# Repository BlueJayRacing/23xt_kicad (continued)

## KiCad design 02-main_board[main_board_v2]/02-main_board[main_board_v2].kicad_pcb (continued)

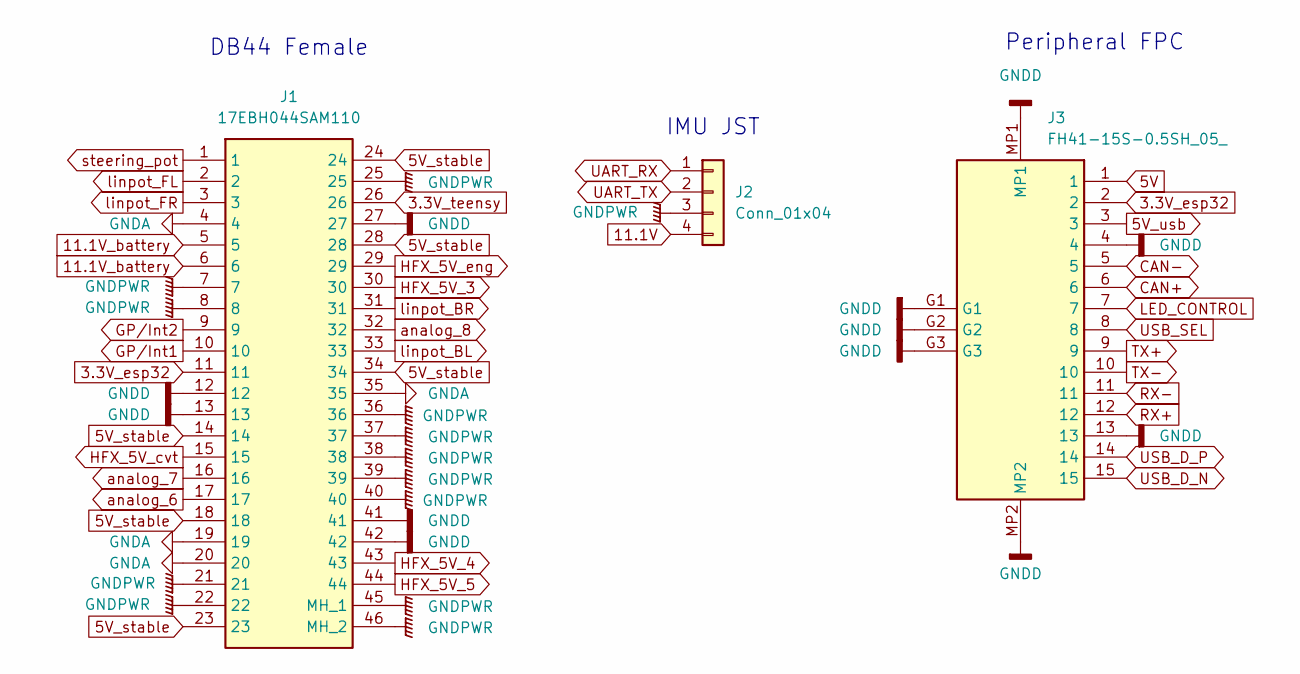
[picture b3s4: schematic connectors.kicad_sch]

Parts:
J1: 17EBH044SAM110; Manufacturer_Part_Number 17EBH044SAM110
J2: Conn_01x04; JST_EH_B4B-EH-A_1x04_P2.50mm_Vertical
J3: FH41-15S-0.5SH_05_; FH4115S05SH05; Mouser Part Number 798-FH4115S05SH05

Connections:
3.3V_esp32: J1.11, J3.2; also elsewhere on the board
3.3V_teensy: J1.26; also elsewhere on the board
5V: J3.1; also elsewhere on the board
5V_stable: J1.14, J1.18, J1.23, J1.24, J1.28, J1.34; also elsewhere on the board
5V_usb: J3.3; also elsewhere on the board
11.1V: J2.4; also elsewhere on the board
11.1V_battery: J1.5, J1.6; also elsewhere on the board
CAN+: J3.6; also elsewhere on the board
CAN-: J3.5; also elsewhere on the board
GNDA: J1.4, J1.7, J1.8, J1.12, J1.13, J1.19, J1.20, J1.21, J1.22, J1.25, J1.27, J1.35, J1.36, J1.37, J1.38, J1.39, J1.40, J1.41, J1.42, J1.45 (MH_1), J1.46 (MH_2), J2.3, J3.4, J3.13, J3.G1, J3.G2, J3.G3, J3.MP1, J3.MP2; also elsewhere on the board
GP/Int1: J1.10; also elsewhere on the board
GP/Int2: J1.9; also elsewhere on the board
HFX_5V_3: J1.30; also elsewhere on the board
HFX_5V_4: J1.43; also elsewhere on the board
HFX_5V_5: J1.44; also elsewhere on the board
HFX_5V_cvt: J1.15; also elsewhere on the board
HFX_5V_eng: J1.29; also elsewhere on the board
LED_CONTROL: J3.7; also elsewhere on the board
RX+: J3.12; also elsewhere on the board
RX-: J3.11; also elsewhere on the board
TX+: J3.9; also elsewhere on the board
TX-: J3.10; also elsewhere on the board
UART_RX: J2.1; also elsewhere on the board
UART_TX: J2.2; also elsewhere on the board
USB_D_N: J3.15; also elsewhere on the board
USB_D_P: J3.14; also elsewhere on the board
USB_SEL: J3.8; also elsewhere on the board
analog_6: J1.17; also elsewhere on the board
analog_7: J1.16; also elsewhere on the board
analog_8: J1.32; also elsewhere on the board
linpot_BL: J1.33; also elsewhere on the board
linpot_BR: J1.31; also elsewhere on the board
linpot_FL: J1.2; also elsewhere on the board
linpot_FR: J1.3; also elsewhere on the board
steering_pot: J1.1; also elsewhere on the board

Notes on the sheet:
DB44 Female
Peripheral FPC
IMU JST

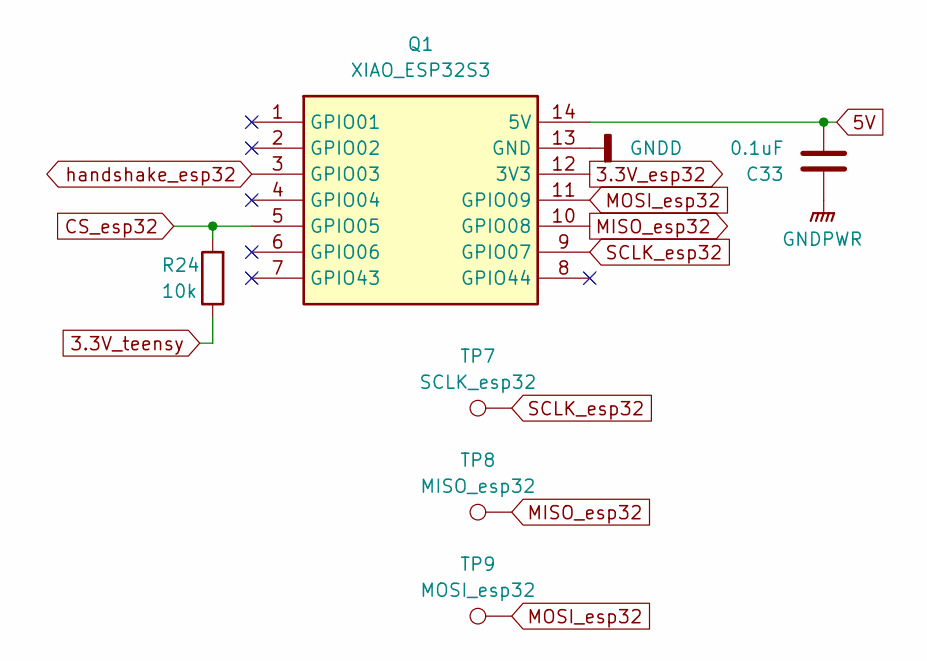
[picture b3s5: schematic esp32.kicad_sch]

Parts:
C33: 0.1uF; C_0603_1608Metric; MPN CC0603KRX7R9BB104; LCSC C14663
Q1: XIAO_ESP32S3; Manufacturer_Part_Number XIAO ESP32S3
R24: 10k; R_0603_1608Metric; MPN CRCW060310K0FKEA; LCSC C25804
TP7: SCLK_esp32; TestPoint_Pad_1.0x1.0mm
TP8: MISO_esp32; TestPoint_Pad_1.0x1.0mm
TP9: MOSI_esp32; TestPoint_Pad_1.0x1.0mm

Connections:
3.3V_esp32: Q1.12 (3V3); also elsewhere on the board
3.3V_teensy: R24.1; also elsewhere on the board
5V: C33.2, Q1.14 (5V); also elsewhere on the board
CS_esp32: Q1.5 (GPIO05), R24.2; also elsewhere on the board
GNDA: C33.1, Q1.13 (GND); also elsewhere on the board
MISO_esp32: Q1.10 (GPIO08), TP8.1 (1_1); also elsewhere on the board
MOSI_esp32: Q1.11 (GPIO09), TP9.1 (1_1); also elsewhere on the board
SCLK_esp32: Q1.9 (GPIO07), TP7.1 (1_1); also elsewhere on the board
handshake_esp32: Q1.3 (GPIO03); also elsewhere on the board

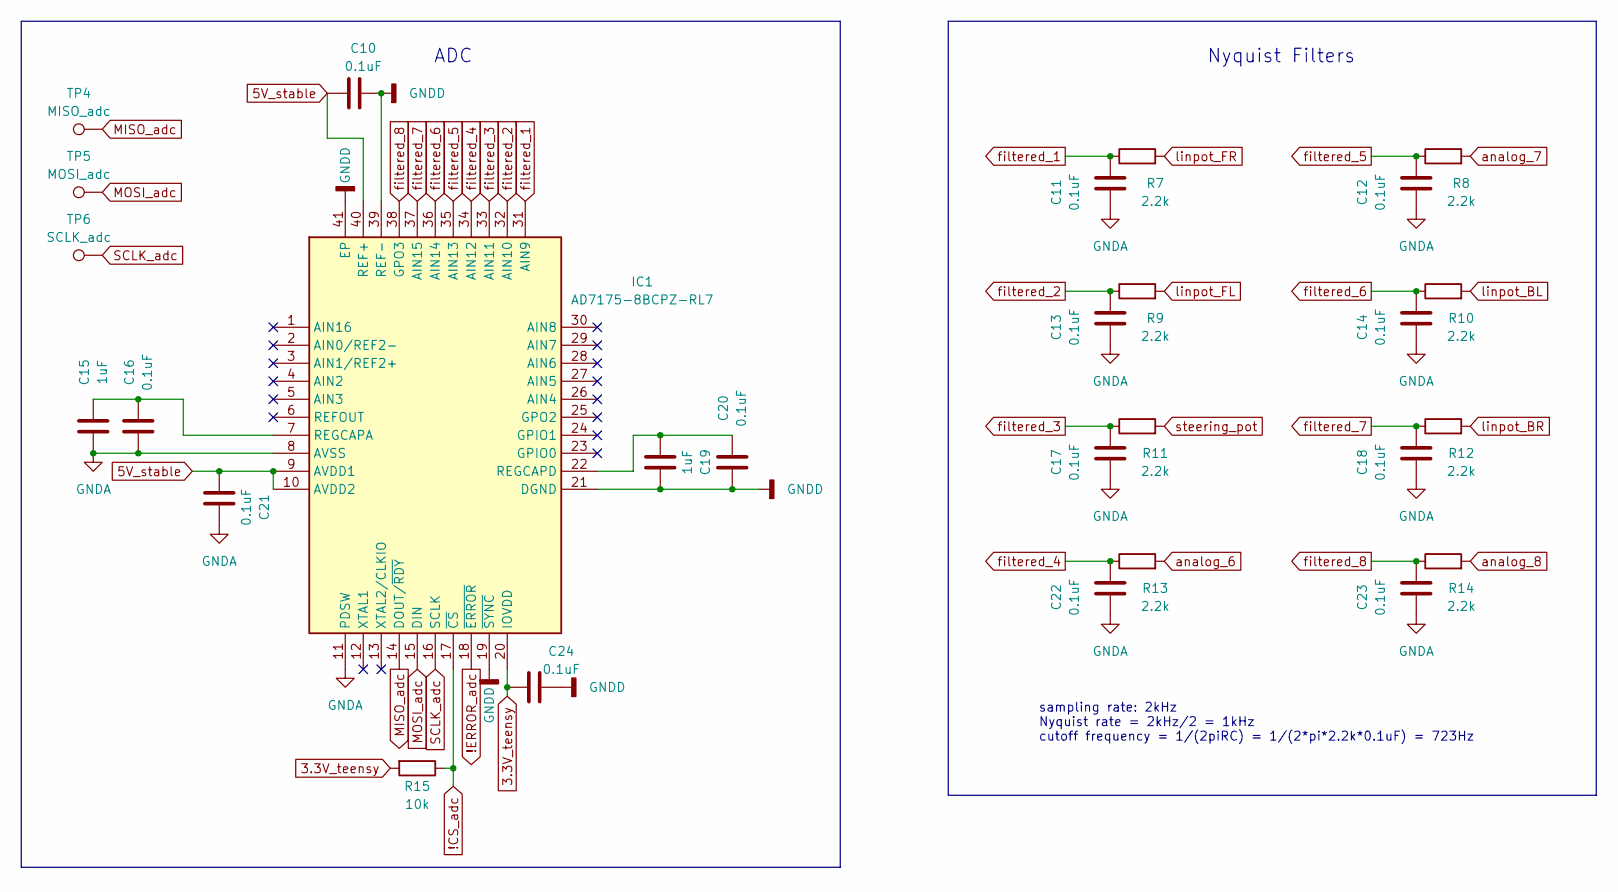
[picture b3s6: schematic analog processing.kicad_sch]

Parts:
C10, C11, C12, C13, C14, C16, C17, C18, C20, C21, C22, C23, C24: 0.1uF; C_0603_1608Metric; MPN CC0603KRX7R9BB104; LCSC C14663
C15, C19: 1uF; C_0603_1608Metric; MPN CL10A105KA8NFNC; LCSC C15849
IC1: AD7175-8BCPZ-RL7; Manufacturer_Part_Number AD7175-8BCPZ-RL7; Mouser Part Number 584-AD7175-8BCPZ-RL7
R7, R8, R9, R10, R11, R12, R13, R14: 2.2k; R_0603_1608Metric; MPN RC0603FR-072K2L; LCSC C4190
R15: 10k; R_0603_1608Metric; MPN CRCW060310K0FKEA; LCSC C25804
TP4: MISO_adc; TestPoint_Pad_1.0x1.0mm
TP5: MOSI_adc; TestPoint_Pad_1.0x1.0mm
TP6: SCLK_adc; TestPoint_Pad_1.0x1.0mm

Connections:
3.3V_teensy: C24.1, IC1.20 (IOVDD), R15.2; also elsewhere on the board
5V_stable: C10.1, C21.1, IC1.9 (AVDD1), IC1.10 (AVDD2), IC1.40 (REF+); also elsewhere on the board
!CS_adc: IC1.17 (~CS), R15.1; also elsewhere on the board
!ERROR_adc: IC1.18 (~ERROR); also elsewhere on the board
GNDA: C10.2, C11.1, C12.1, C13.1, C14.1, C15.1, C16.1, C17.1, C18.1, C19.2, C20.1, C21.2, C22.1, C23.1, C24.2, IC1.8 (AVSS), IC1.11 (PDSW), IC1.19 (~SYNC), IC1.21 (DGND), IC1.39 (REF-), IC1.41 (EP); also elsewhere on the board
MISO_adc: IC1.14 (DOUT/~RDY), TP4.1 (1_1); also elsewhere on the board
MOSI_adc: IC1.15 (DIN), TP5.1 (1_1); also elsewhere on the board
unnamed: C15.2, C16.2, IC1.7 (REGCAPA)
unnamed: C19.1, C20.2, IC1.22 (REGCAPD)
SCLK_adc: IC1.16 (SCLK), TP6.1 (1_1); also elsewhere on the board
analog_6: R13.2; also elsewhere on the board
analog_7: R8.2; also elsewhere on the board
analog_8: R14.2; also elsewhere on the board
filtered_1: C11.2, IC1.31 (AIN9), R7.1
filtered_2: C13.2, IC1.32 (AIN10), R9.1
filtered_3: C17.2, IC1.33 (AIN11), R11.1
filtered_4: C22.2, IC1.34 (AIN12), R13.1
filtered_5: C12.2, IC1.35 (AIN13), R8.1
filtered_6: C14.2, IC1.36 (AIN14), R10.1
filtered_7: C18.2, IC1.37 (AIN15), R12.1
filtered_8: C23.2, IC1.38 (GPO3), R14.1
linpot_BL: R10.2; also elsewhere on the board
linpot_BR: R12.2; also elsewhere on the board
linpot_FL: R9.2; also elsewhere on the board
linpot_FR: R7.2; also elsewhere on the board
steering_pot: R11.2; also elsewhere on the board

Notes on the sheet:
Nyquist Filters
sampling rate: 2kHz Nyquist rate = 2kHz/2 = 1kHz cutoff frequency = 1/(2piRC) = 1/(2*pi*2.2k*0.1uF) = 723Hz
ADC

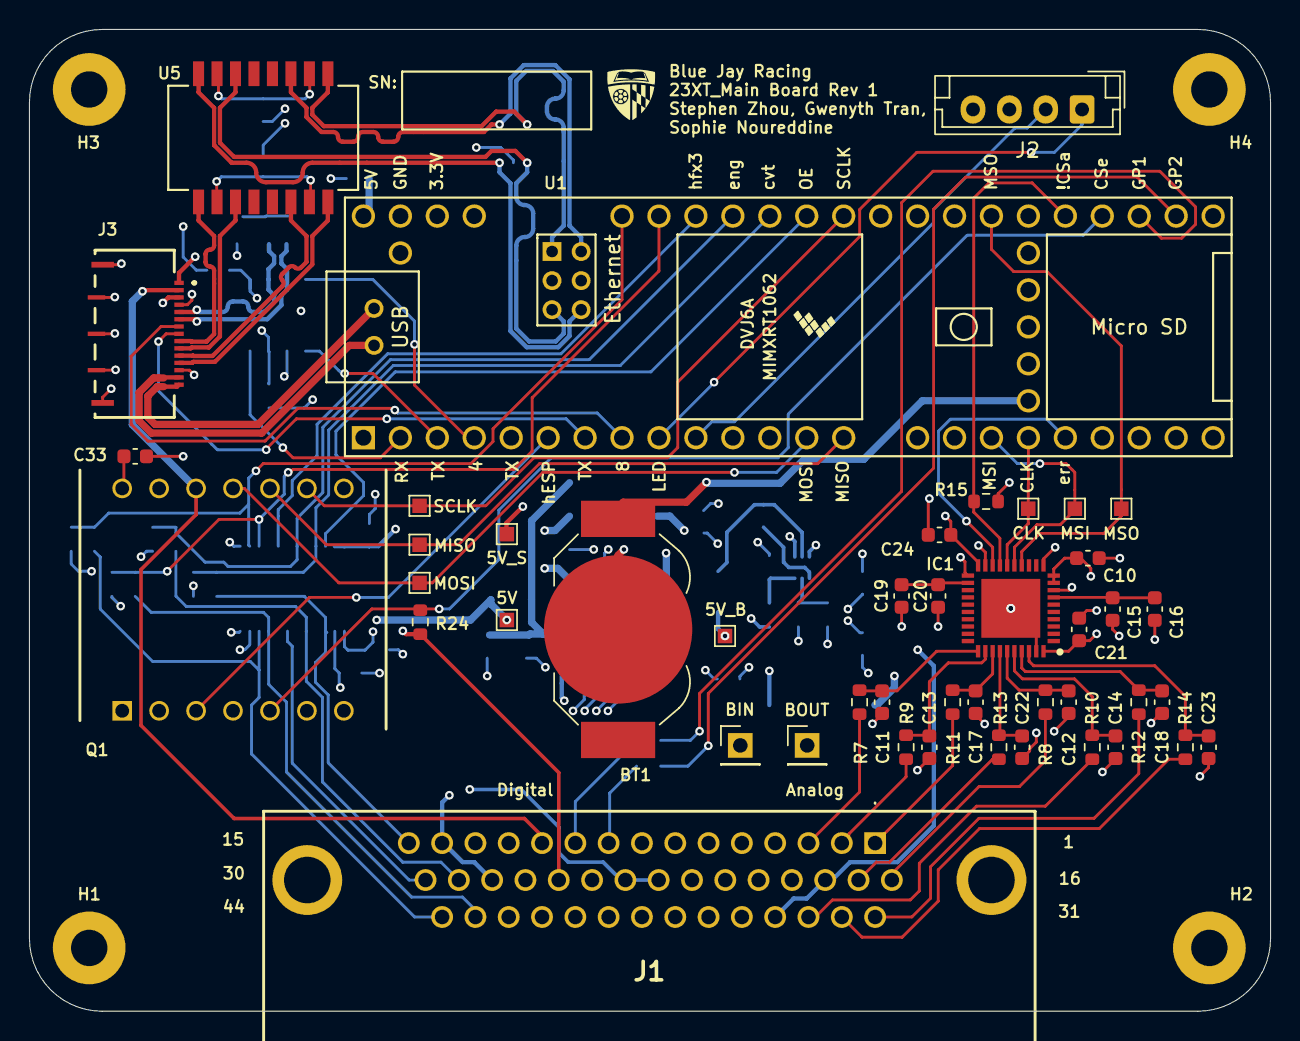
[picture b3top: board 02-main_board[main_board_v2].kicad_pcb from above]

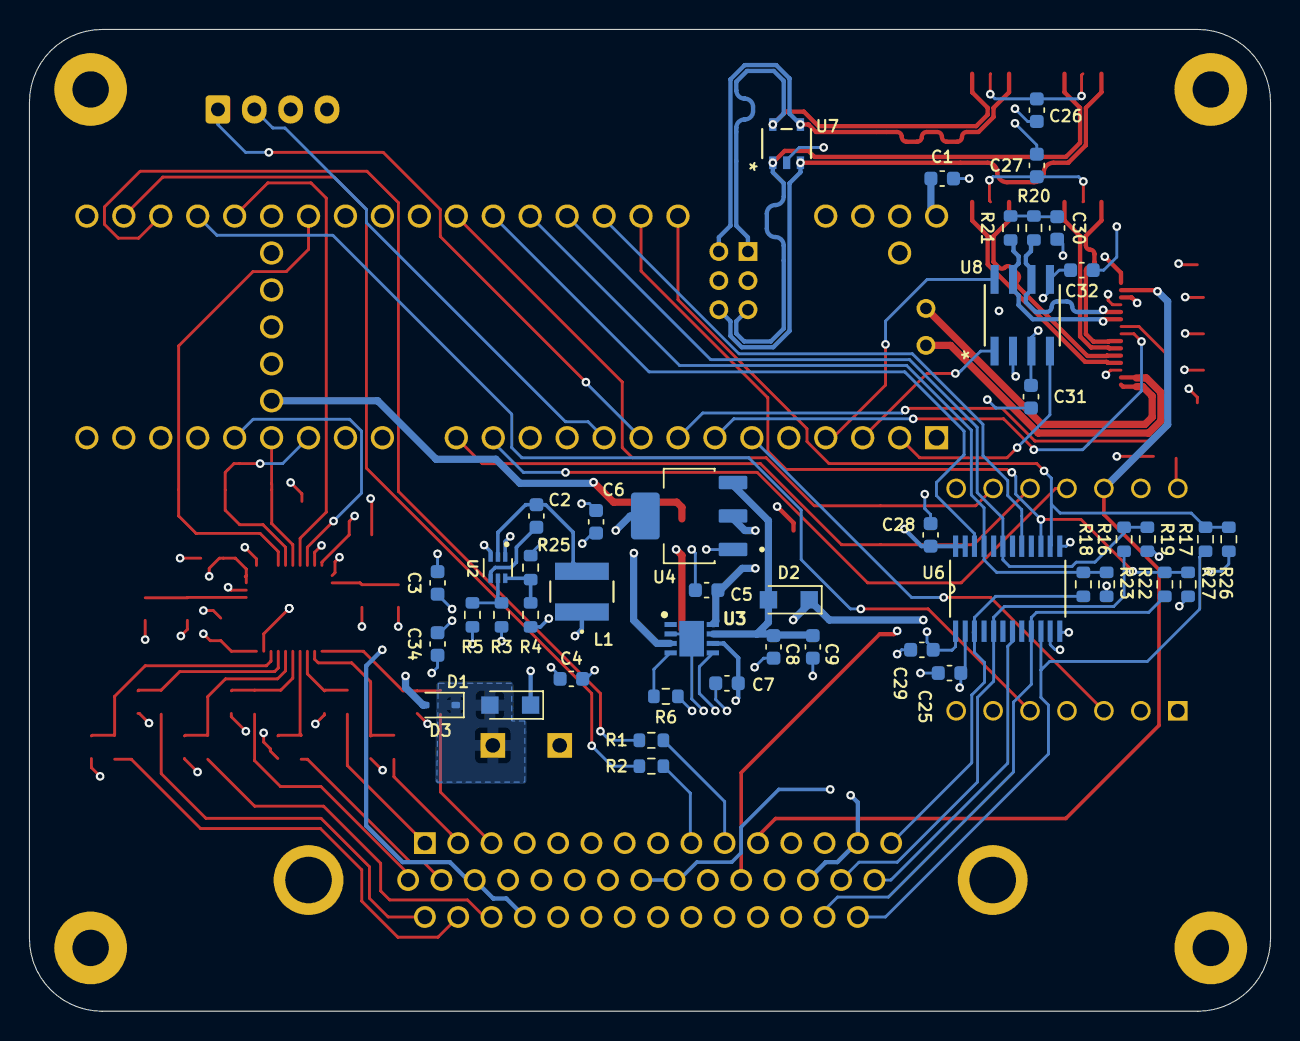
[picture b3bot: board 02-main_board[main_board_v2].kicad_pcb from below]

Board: 4 copper layers, 85.3 x 67.5 mm, 94 parts (45 on the bottom side), 82 nets.

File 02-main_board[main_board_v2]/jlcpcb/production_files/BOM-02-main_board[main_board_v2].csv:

Comment,Designator,Footprint,LCSC,Quantity
0.1uF,"C1,C10,C11,C12,C13,C14,C16,C17,C18,C2,C20,C21,C22,C23,C24,C25,C26,C27,C28,C29,C30,C31,C32,C33,C34,C5,C7,C8",C_0603_1608Metric,C14663,28
10k,"R15,R24,R3",R_0603_1608Metric,C25804,3
10uF,C3,C_0603_1608Metric,C96446,1
12k,R5,R_0603_1608Metric,C22790,1
1uF,"C15,C19,C6,C9",C_0603_1608Metric,C15849,4
2.2k,"R10,R11,R12,R13,R14,R7,R8,R9",R_0603_1608Metric,C4190,8
22uF,C4,C_0603_1608Metric,C59461,1
3.3uH,L1,IND_TAIYO_NRS4018_TAY,C92960,1
400,R6,R_0603_1608Metric,C5841024,1
47,"R1,R2",R_0603_1608Metric,C23182,2
74LVC4245APW_118,U6,74LVC4245APW_118,C6091,1
AD7175-8BCPZ-RL7,IC1,AD7175-8BCPZ-RL7,C578395,1
ATA6561-GAQW-N,U8,ATA6561-GAQW-N,C616016,1
ESD12VD3B-TP,D3,D_SOD-323,C435886,1
LDL1117S50R_,U4,LDL1117S50R_,C970558,1
PMEG60T20ELR-QX,D1,Nexperia_CFP3_SOD-123W,C6629174,1
PT61018PEL,U5,SOIC_PT61018PEL,C840586,1
RCLAMP3354S_TCT,U7,RCLAMP3354S_TCT,C441850,1
TPS2115ADRBRT,U3,SON65P300X300X100-9N-D,C140321,1
TPS562242DRLR,U2,SOT50P160X60-6N,C19272253,1
345k,R4,R_0603_1608Metric,,1

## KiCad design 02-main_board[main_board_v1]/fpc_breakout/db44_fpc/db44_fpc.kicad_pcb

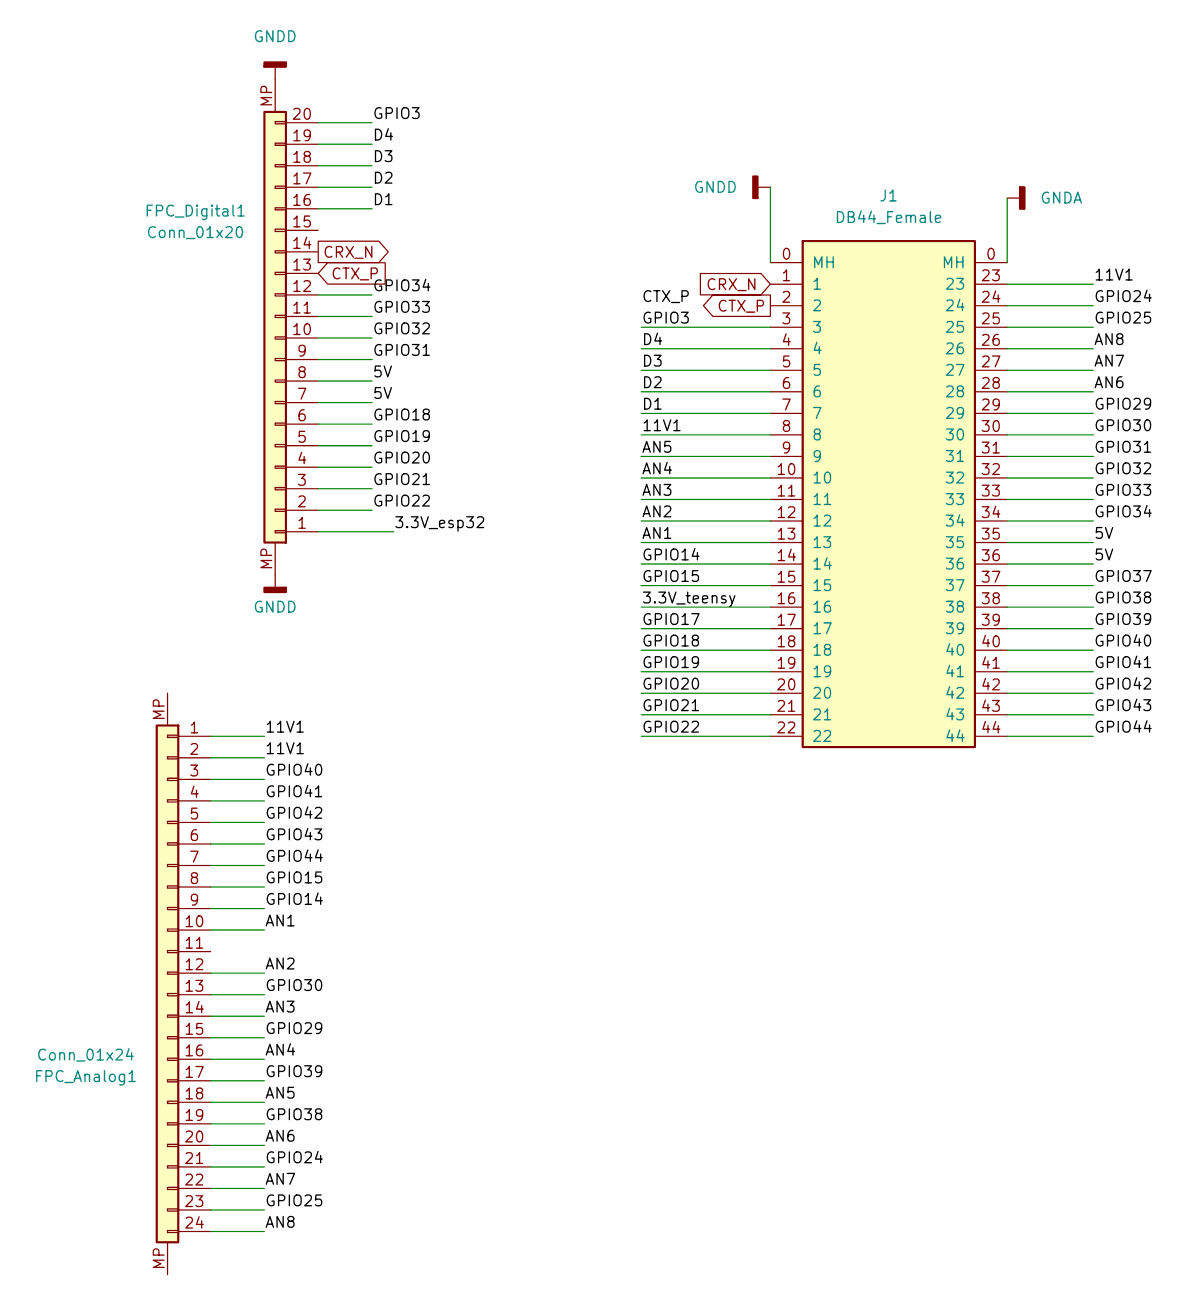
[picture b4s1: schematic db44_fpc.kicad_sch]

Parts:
FPC_Analog1: Conn_01x24; TE_2-84953-4_1x24-1MP_P1.0mm_Horizontal
FPC_Digital1: Conn_01x20; TE_2-84953-0_1x20-1MP_P1.0mm_Horizontal
J1: DB44_Female; DSUB-44-HD_Socket_Vertical_P2.29x1.98mm_MountingHoles

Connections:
/3.3V_esp32: FPC_Digital1.1
/3.3V_teensy: J1.16
/5V: FPC_Digital1.7, FPC_Digital1.8, J1.35, J1.36
/11V1: FPC_Analog1.1, FPC_Analog1.2, J1.8, J1.23
/AN1: FPC_Analog1.10, J1.13
/AN2: FPC_Analog1.12, J1.12
/AN3: FPC_Analog1.14, J1.11
/AN4: FPC_Analog1.16, J1.10
/AN5: FPC_Analog1.18, J1.9
/AN6: FPC_Analog1.20, J1.28
/AN7: FPC_Analog1.22, J1.27
/AN8: FPC_Analog1.24, J1.26
/D1: FPC_Digital1.16, J1.7
/D2: FPC_Digital1.17, J1.6
/D3: FPC_Digital1.18, J1.5
/D4: FPC_Digital1.19, J1.4
/GPIO3: FPC_Digital1.20, J1.3
/GPIO14: FPC_Analog1.9, J1.14
/GPIO15: FPC_Analog1.8, J1.15
/GPIO17: J1.17
/GPIO18: FPC_Digital1.6, J1.18
/GPIO19: FPC_Digital1.5, J1.19
/GPIO20: FPC_Digital1.4, J1.20
/GPIO21: FPC_Digital1.3, J1.21
/GPIO22: FPC_Digital1.2, J1.22
/GPIO24: FPC_Analog1.21, J1.24
/GPIO25: FPC_Analog1.23, J1.25
/GPIO29: FPC_Analog1.15, J1.29
/GPIO30: FPC_Analog1.13, J1.30
/GPIO31: FPC_Digital1.9, J1.31
/GPIO32: FPC_Digital1.10, J1.32
/GPIO33: FPC_Digital1.11, J1.33
/GPIO34: FPC_Digital1.12, J1.34
/GPIO37: J1.37
/GPIO38: FPC_Analog1.19, J1.38
/GPIO39: FPC_Analog1.17, J1.39
/GPIO40: FPC_Analog1.3, J1.40
/GPIO41: FPC_Analog1.4, J1.41
/GPIO42: FPC_Analog1.5, J1.42
/GPIO43: FPC_Analog1.6, J1.43
/GPIO44: FPC_Analog1.7, J1.44
CRX_N: FPC_Digital1.14, J1.1
CTX_P: FPC_Digital1.13, J1.2
GNDD: FPC_Digital1.MP, J1.0 (MH)

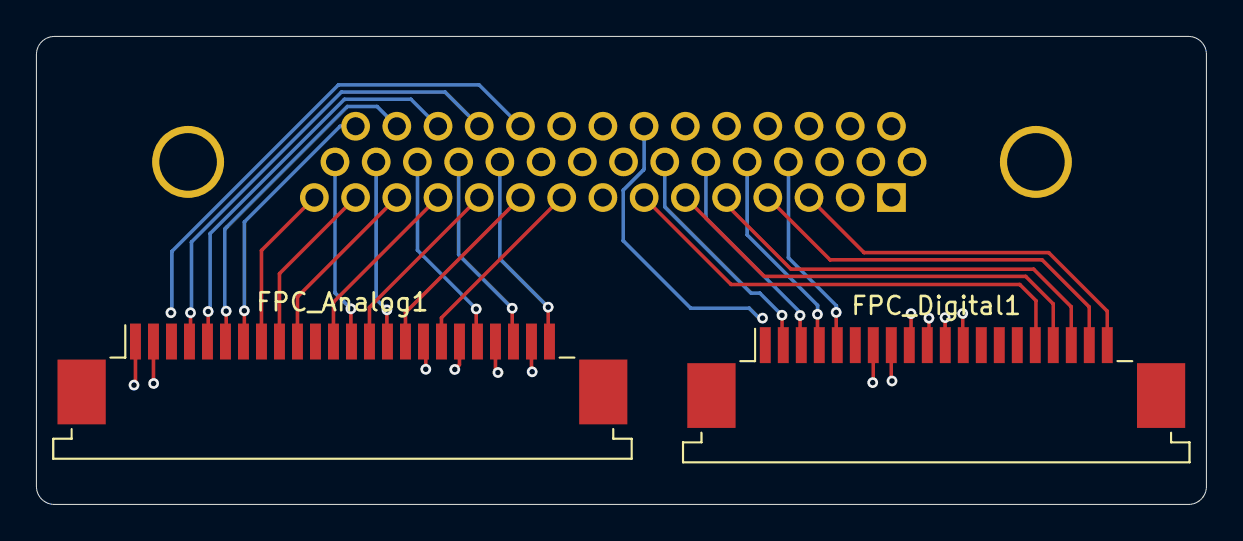
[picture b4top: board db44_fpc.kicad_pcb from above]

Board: 4 copper layers, 65.0 x 26.0 mm, 3 parts (1 on the bottom side), 39 nets.

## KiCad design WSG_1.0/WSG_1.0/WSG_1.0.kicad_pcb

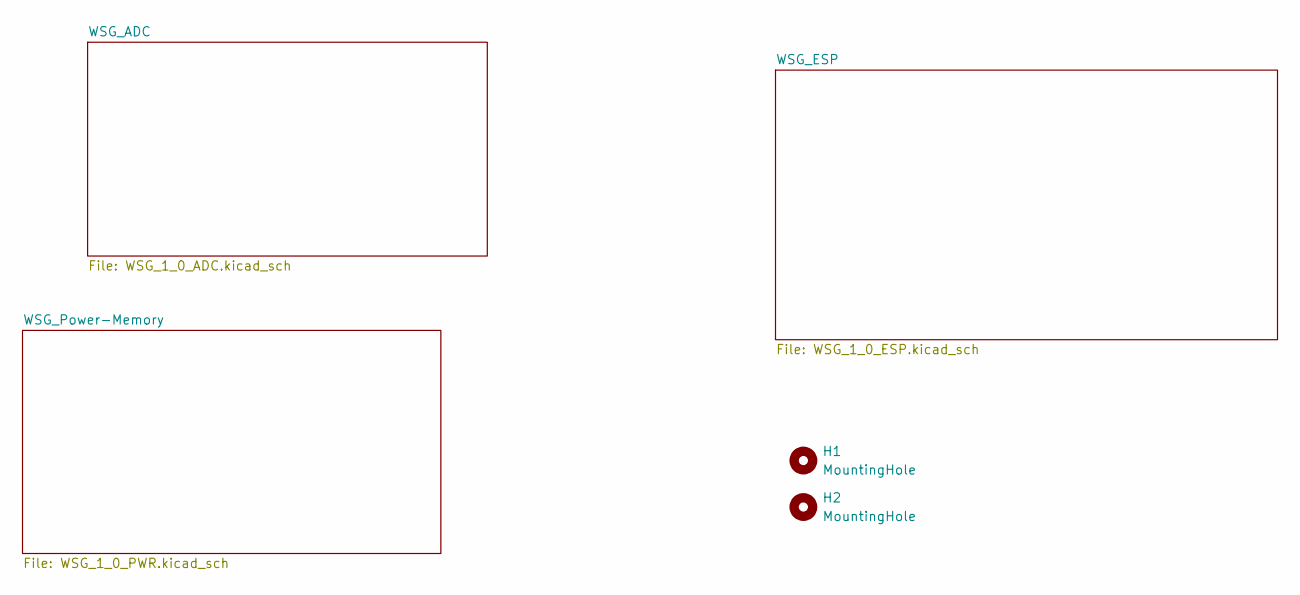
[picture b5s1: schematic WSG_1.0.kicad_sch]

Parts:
H1, H2: MountingHole; MountingHole_3.2mm_M3

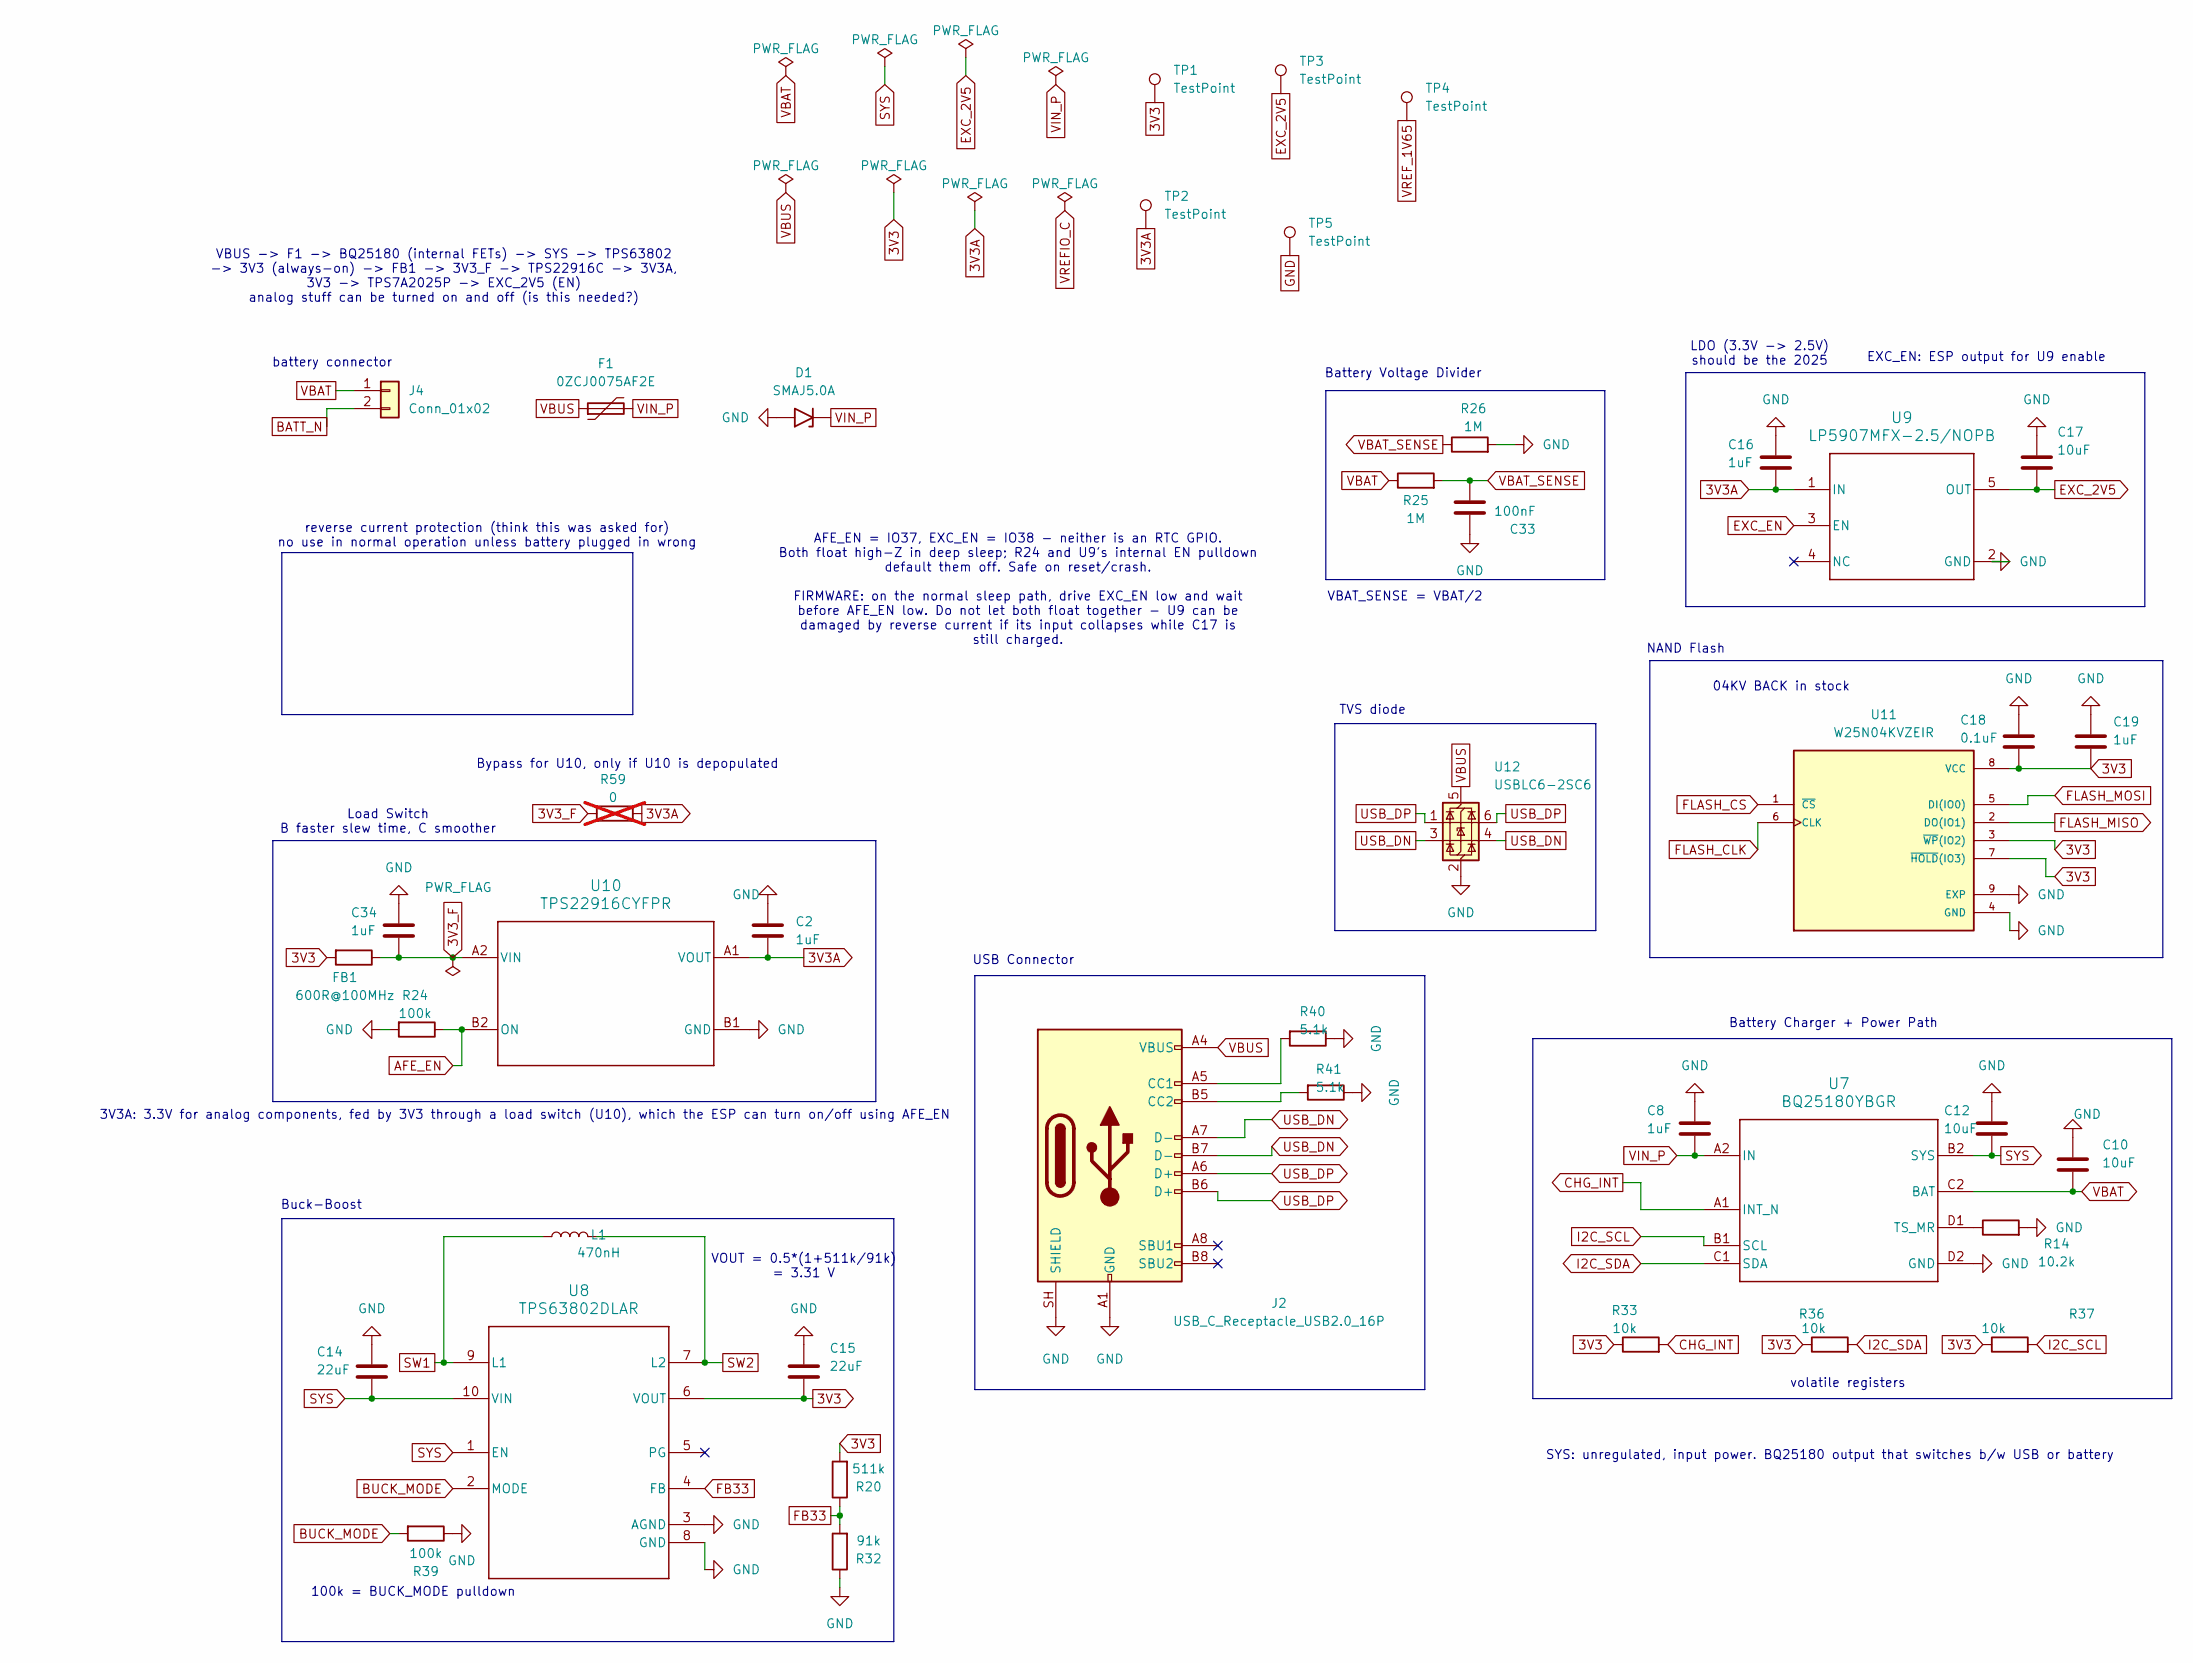
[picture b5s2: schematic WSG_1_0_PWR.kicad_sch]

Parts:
C2, C8, C16, C19, C34: 1uF; C_0402_1005Metric_Pad0.74x0.62mm_HandSolder
C10, C12: 10uF; C_0402_1005Metric_Pad0.74x0.62mm_HandSolder
C14, C15: 22uF; C_0603_1608Metric_Pad1.08x0.95mm_HandSolder; MPN CL10A226MQ8NRNE
C17: 10uF; C_0603_1608Metric_Pad1.08x0.95mm_HandSolder; MPN GRM188R60J106ME84
C18: 0.1uF; C_0402_1005Metric_Pad0.74x0.62mm_HandSolder
C33: 100nF; C_0402_1005Metric_Pad0.74x0.62mm_HandSolder
D1: SMAJ5.0A; D_SMA
F1: 0ZCJ0075AF2E; Fuse_1206_3216Metric
FB1: 600R@100MHz; L_0402_1005Metric; MPN BLM15AG601SN1D
J2: USB_C_Receptacle_USB2.0_16P; USB_C_Receptacle_GCT_USB4110; MPN USB4110-GF-A
J4: Conn_01x02; JST_S2B-PH-K-S_LF__SN_-2pin_male
L1: 470nH; L_Coilcraft_XxL4020; MPN XGL4020-471MEC
R14: 10.2k; R_0402_1005Metric_Pad0.72x0.64mm_HandSolder
R20: 511k; R_0402_1005Metric_Pad0.72x0.64mm_HandSolder
R24, R39: 100k; R_0402_1005Metric_Pad0.72x0.64mm_HandSolder
R25, R26: 1M; R_0402_1005Metric_Pad0.72x0.64mm_HandSolder
R32: 91k; R_0402_1005Metric_Pad0.72x0.64mm_HandSolder
R33, R36, R37: 10k; R_0402_1005Metric_Pad0.72x0.64mm_HandSolder
R40, R41: 5.1k; R_0402_1005Metric_Pad0.72x0.64mm_HandSolder
R59: 0; R_0402_1005Metric_Pad0.72x0.64mm_HandSolder; not fitted
TP1, TP2, TP3, TP4, TP5: TestPoint; TestPoint_Pad_1.0x1.0mm
U7: BQ25180YBGR; IC_BQ25180YBGR
U8: TPS63802DLAR; DLA0010A
U9: LP5907MFX-2.5/NOPB; SOT-23-5
U10: TPS22916CYFPR; IC_TPS22916BYFPR
U11: W25N04KVZEIR; IC_W25N04KVZEIR; PARTREV I
U12: USBLC6-2SC6; SOT-23-6

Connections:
3V3: C15.2, C18.2, C19.2, FB1.2, R20.2, R33.1, R36.1, R37.1, TP1.1 (1_1), U8.6 (VOUT), U11.3 (~WP(IO2)), U11.7 (~HOLD(IO3)), U11.8 (VCC); also elsewhere on the board
3V3A: C2.2, C16.2, R59.1, TP2.1 (1_1), U9.1 (IN), U10.A1 (VOUT); also elsewhere on the board
3V3_F: C34.2, FB1.1, R59.2, U10.A2 (VIN)
AFE_EN: R24.1, U10.B2 (ON); also elsewhere on the board
BATT_N: J4.2; also elsewhere on the board
BUCK_MODE: R39.2, U8.2 (MODE); also elsewhere on the board
CHG_INT: R33.2, U7.A1 (INT_N); also elsewhere on the board
EXC_2V5: C17.2, TP3.1 (1_1), U9.5 (OUT); also elsewhere on the board
EXC_EN: U9.3 (EN); also elsewhere on the board
FB33: R20.1, R32.2, U8.4 (FB)
FLASH_CLK: U11.6 (CLK); also elsewhere on the board
FLASH_CS: U11.1 (~CS); also elsewhere on the board
FLASH_MISO: U11.2 (DO(IO1)); also elsewhere on the board
FLASH_MOSI: U11.5 (DI(IO0)); also elsewhere on the board
GND: C2.1, C8.1, C10.1, C12.1, C14.1, C15.1, C16.1, C17.1, C18.1, C19.1, C33.2, C34.1, D1.2 (A2), J2.A1 (GND), J2.A12 (GND), J2.B1 (GND), J2.B12 (GND), J2.SH (SHIELD), R14.2, R24.2, R26.2, R32.1, R39.1, R40.1, R41.1, TP5.1 (1_1), U7.D2 (GND), U8.3 (AGND), U8.8 (GND), U9.2 (GND), U10.B1 (GND), U11.4 (GND), U11.9 (EXP), U12.2 (GND); also elsewhere on the board
I2C_SCL: R37.2, U7.B1 (SCL); also elsewhere on the board
I2C_SDA: R36.2, U7.C1 (SDA); also elsewhere on the board
unnamed: J2.A5 (CC1), R40.2
unnamed: J2.B5 (CC2), R41.2
unnamed: R14.1, U7.D1 (TS_MR)
SW1: L1.1, U8.9 (L1)
SW2: L1.2, U8.7 (L2)
SYS: C12.2, C14.2, U7.B2 (SYS), U8.1 (EN), U8.10 (VIN)
USB_DN: J2.A7 (D-), J2.B7 (D-), U12.3 (I/O2), U12.4 (I/O2); also elsewhere on the board
USB_DP: J2.A6 (D+), J2.B6 (D+), U12.1 (I/O1), U12.6 (I/O1); also elsewhere on the board
VBAT: C10.2, J4.1, R25.1, U7.C2 (BAT)
VBAT_SENSE: C33.1, R25.2, R26.1; also elsewhere on the board
VBUS: F1.1, J2.A4 (VBUS), J2.A9 (VBUS), J2.B4 (VBUS), J2.B9 (VBUS), U12.5 (VBUS)
VIN_P: C8.2, D1.1 (A1), F1.2, U7.A2 (IN)
VREF_1V65: TP4.1 (1_1); also elsewhere on the board

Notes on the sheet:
3V3A: 3.3V for analog components, fed by 3V3 through a load switch (U10), which the ESP can turn on/off using AFE_EN
100k = BUCK_MODE pulldown
LDO (3.3V -> 2.5V) should be the 2025
04KV BACK in stock
Battery Voltage Divider
NAND Flash
VBAT_SENSE = VBAT/2
volatile registers
EXC_EN: ESP output for U9 enable
Load Switch B faster slew time, C smoother
Battery Charger + Power Path
VBUS -> F1 -> BQ25180 (internal FETs) -> SYS -> TPS63802 -> 3V3 (always-on) -> FB1 -> 3V3_F -> TPS22916C -> 3V3A, 3V3 -> TPS7A2025P -> EXC_2V5 (EN) analog stuff can be turned on and off (is this needed?)
AFE_EN = IO37, EXC_EN = IO38 - neither is an RTC GPIO. Both float high-Z in deep sleep; R24 and U9's internal EN pulldown default them off. Safe on reset/crash. FIRMWARE: on the normal sleep path, drive EXC_EN low and wait before AFE_EN low. Do not let both float together - U9 can be damaged by rev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
Buck-Boost
USB Connector
battery connector
reverse current protection (think this was asked for) no use in normal operation unless battery plugged in wrong
SYS: unregulated, input power. BQ25180 output that switches b/w USB or battery
TVS diode
Bypass for U10, only if U10 is depopulated
VOUT = 0.5*(1+511k/91k) = 3.31 V

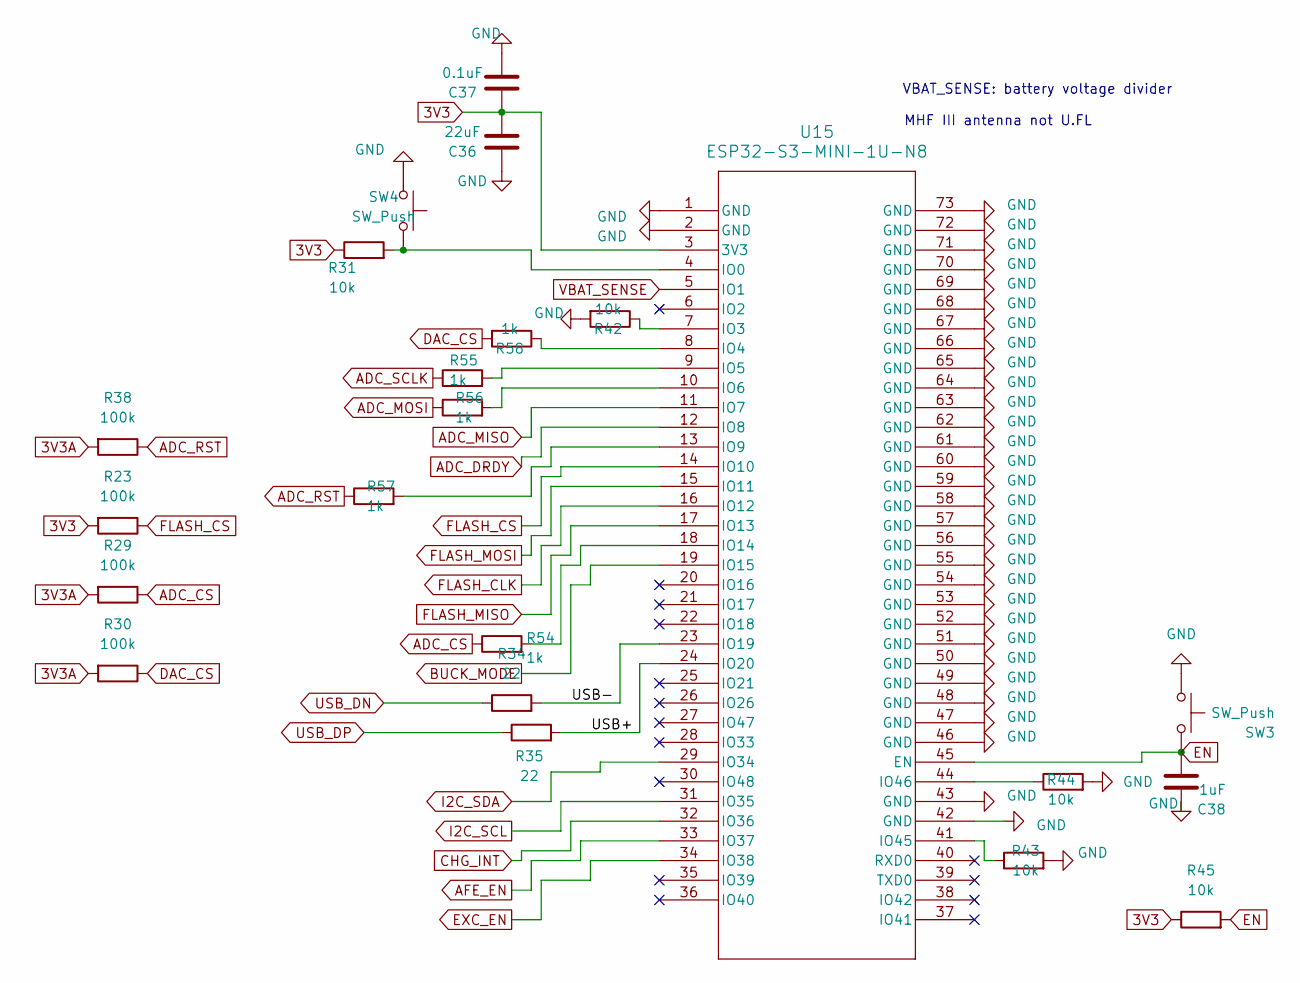
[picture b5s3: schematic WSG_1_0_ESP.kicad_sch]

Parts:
C36: 22uF; C_0603_1608Metric_Pad1.08x0.95mm_HandSolder; MPN CL10A226MQ8NRNE
C37: 0.1uF; C_0402_1005Metric_Pad0.74x0.62mm_HandSolder
C38: 1uF; C_0402_1005Metric_Pad0.74x0.62mm_HandSolder
R23, R29, R30, R38: 100k; R_0402_1005Metric_Pad0.72x0.64mm_HandSolder
R31, R42, R43, R44, R45: 10k; R_0402_1005Metric_Pad0.72x0.64mm_HandSolder
R34, R35: 22; R_0402_1005Metric_Pad0.72x0.64mm_HandSolder
R54, R55, R56, R57, R58: 1k; R_0402_1005Metric_Pad0.72x0.64mm_HandSolder
SW3, SW4: SW_Push; NANOT100AS_butt
U15: ESP32-S3-MINI-1U-N8; ESP32-S3-MINI-1U_EXP

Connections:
3V3: C36.1, C37.1, R23.2, R31.1, R45.1, U15.3 (3V3); also elsewhere on the board
3V3A: R29.2, R30.2, R38.2; also elsewhere on the board
/WSG_ESP/USB+: R35.2, U15.24 (IO20)
/WSG_ESP/USB-: R34.2, U15.23 (IO19)
ADC_CS: R29.1, R54.1; also elsewhere on the board
ADC_DRDY: U15.12 (IO8); also elsewhere on the board
ADC_MISO: U15.11 (IO7); also elsewhere on the board
ADC_MOSI: R56.1; also elsewhere on the board
ADC_RST: R38.1, R57.1; also elsewhere on the board
ADC_SCLK: R55.1; also elsewhere on the board
AFE_EN: U15.33 (IO37); also elsewhere on the board
BUCK_MODE: U15.19 (IO15); also elsewhere on the board
CHG_INT: U15.32 (IO36); also elsewhere on the board
DAC_CS: R30.1, R58.2; also elsewhere on the board
EN: C38.2, R45.2, SW3.2, U15.45 (EN)
EXC_EN: U15.34 (IO38); also elsewhere on the board
FLASH_CLK: U15.16 (IO12); also elsewhere on the board
FLASH_CS: R23.1, U15.14 (IO10); also elsewhere on the board
FLASH_MISO: U15.17 (IO13); also elsewhere on the board
FLASH_MOSI: U15.15 (IO11); also elsewhere on the board
GND: C36.2, C37.2, C38.1, R42.2, R43.2, R44.2, SW3.1, SW4.1, U15.1 (GND), U15.2 (GND), U15.42 (GND), U15.43 (GND), U15.46 (GND), U15.47 (GND), U15.48 (GND), U15.49 (GND), U15.50 (GND), U15.51 (GND), U15.52 (GND), U15.53 (GND), U15.54 (GND), U15.55 (GND), U15.56 (GND), U15.57 (GND), U15.58 (GND), U15.59 (GND), U15.60 (GND), U15.61 (GND), U15.62 (GND), U15.63 (GND), U15.64 (GND), U15.65 (GND), U15.66 (GND), U15.67 (GND), U15.68 (GND), U15.69 (GND), U15.70 (GND), U15.71 (GND), U15.72 (GND), U15.73 (GND); also elsewhere on the board
I2C_SCL: U15.31 (IO35); also elsewhere on the board
I2C_SDA: U15.29 (IO34); also elsewhere on the board
unnamed: R31.2, SW4.2, U15.4 (IO0)
unnamed: R42.1, U15.7 (IO3)
unnamed: R58.1, U15.8 (IO4)
unnamed: R55.2, U15.9 (IO5)
unnamed: R56.2, U15.10 (IO6)
unnamed: R57.2, U15.13 (IO9)
unnamed: R54.2, U15.18 (IO14)
unnamed: R43.1, U15.41 (IO45)
unnamed: R44.1, U15.44 (IO46)
USB_DN: R34.1; also elsewhere on the board
USB_DP: R35.1; also elsewhere on the board
VBAT_SENSE: U15.5 (IO1); also elsewhere on the board

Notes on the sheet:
MHF III antenna not U.FL
VBAT_SENSE: battery voltage divider
